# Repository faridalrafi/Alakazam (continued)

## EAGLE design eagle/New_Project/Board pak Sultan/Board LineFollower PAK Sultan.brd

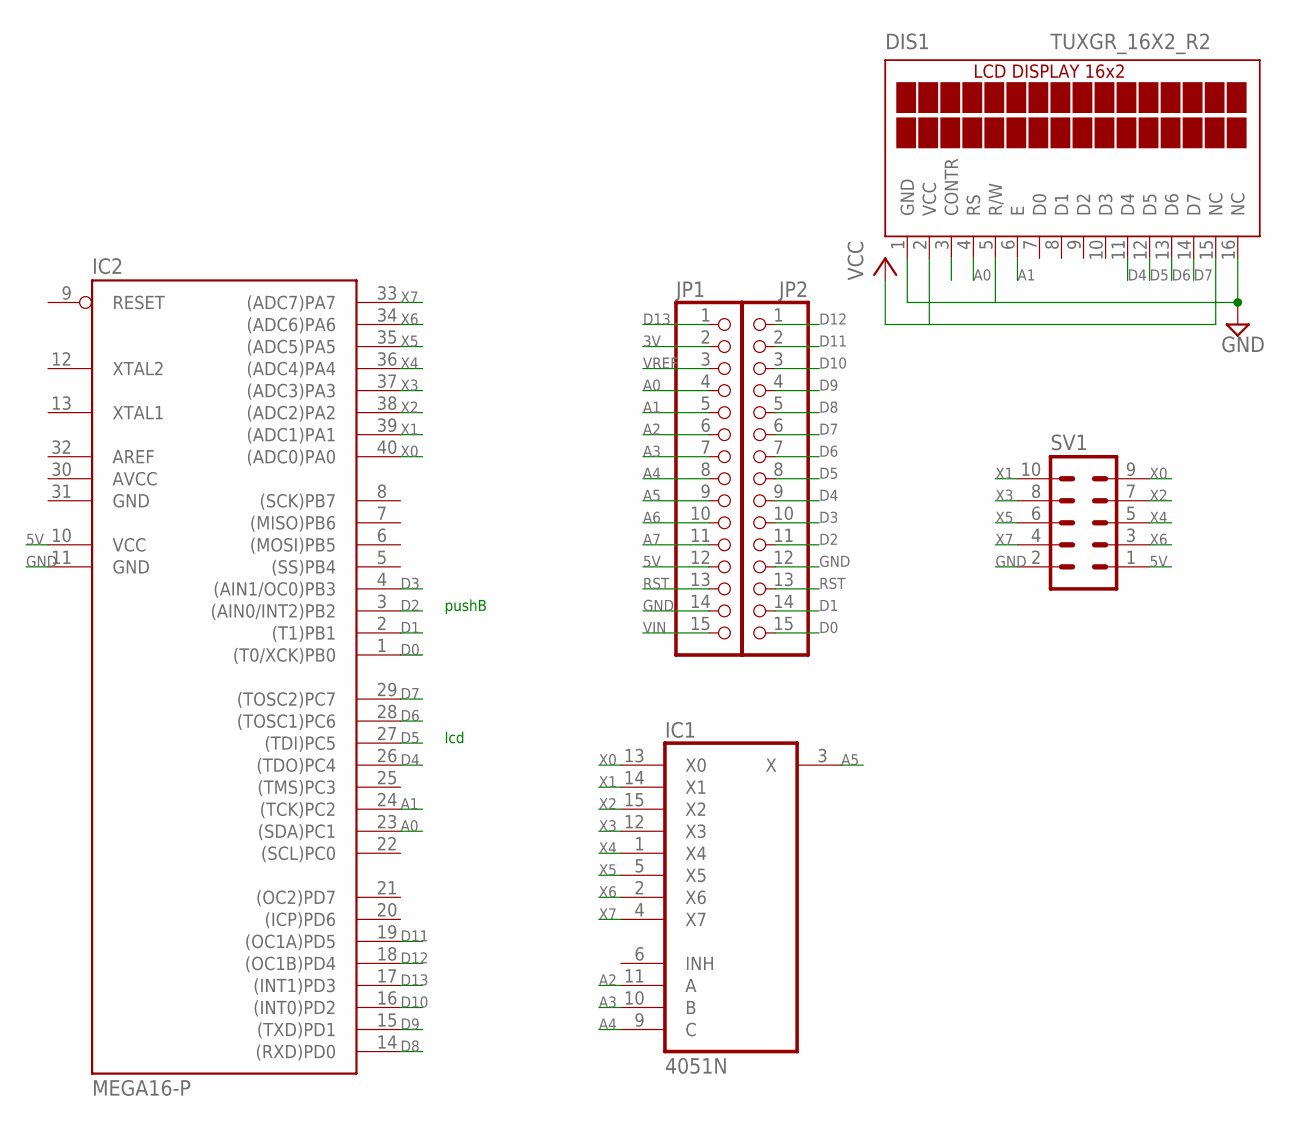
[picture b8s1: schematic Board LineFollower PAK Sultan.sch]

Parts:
DIS1: TUXGR_16X2_R2
IC1: 4051N; DIL16
IC2: MEGA16-P; DIL40
JP1, JP2: PINHD-1X15; 1X15
SV1: MA05-2

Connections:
3V: JP1.2
5V: IC2.10 (VCC), JP1.12, SV1.1
A0: DIS1.4 (RS), IC2.23 ((SDA)PC1), JP1.4
A1: DIS1.6 (E), IC2.24 ((TCK)PC2), JP1.5
A2: IC1.11 (A), JP1.6
A3: IC1.10 (B), JP1.7
A4: IC1.9 (C), JP1.8
A5: IC1.3 (X), JP1.9
A6: JP1.10
A7: JP1.11
AVCC: IC2.30 (AVCC)
D0: IC2.1 ((T0/XCK)PB0), JP2.15
D1: IC2.2 ((T1)PB1), JP2.14
D2: IC2.3 ((AIN0/INT2)PB2), JP2.11
D3: IC2.4 ((AIN1/OC0)PB3), JP2.10
D4: DIS1.11 (D4), IC2.26 ((TDO)PC4), JP2.9
D5: DIS1.12 (D5), IC2.27 ((TDI)PC5), JP2.8
D6: DIS1.13 (D6), IC2.28 ((TOSC1)PC6), JP2.7
D7: DIS1.14 (D7), IC2.29 ((TOSC2)PC7), JP2.6
D8: IC2.14 ((RXD)PD0), JP2.5
D9: IC2.15 ((TXD)PD1), JP2.4
D10: IC2.16 ((INT0)PD2), JP2.3
D11: IC2.19 ((OC1A)PD5), JP2.2
D12: IC2.18 ((OC1B)PD4), JP2.1
D13: IC2.17 ((INT1)PD3), JP1.1
GND: DIS1.1 (GND), DIS1.5 (R/W), DIS1.16 (NC), IC1.8 (GND), IC2.11 (GND), IC2.31 (GND), JP1.14, JP2.12, SV1.2
RST: JP1.13, JP2.13
VCC: DIS1.2 (VCC), DIS1.15 (NC), IC1.16 (VCC)
VEE: IC1.7 (VEE)
VIN: JP1.15
VREF: JP1.3
X0: IC1.13 (X0), IC2.40 ((ADC0)PA0), SV1.9
X1: IC1.14 (X1), IC2.39 ((ADC1)PA1), SV1.10
X2: IC1.15 (X2), IC2.38 ((ADC2)PA2), SV1.7
X3: IC1.12 (X3), IC2.37 ((ADC3)PA3), SV1.8
X4: IC1.1 (X4), IC2.36 ((ADC4)PA4), SV1.5
X5: IC1.5 (X5), IC2.35 ((ADC5)PA5), SV1.6
X6: IC1.2 (X6), IC2.34 ((ADC6)PA6), SV1.3
X7: IC1.4 (X7), IC2.33 ((ADC7)PA7), SV1.4

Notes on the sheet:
pushB
lcd

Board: 2 copper layers, 6 parts (1 on the bottom side), 32 nets, no tracks yet.
